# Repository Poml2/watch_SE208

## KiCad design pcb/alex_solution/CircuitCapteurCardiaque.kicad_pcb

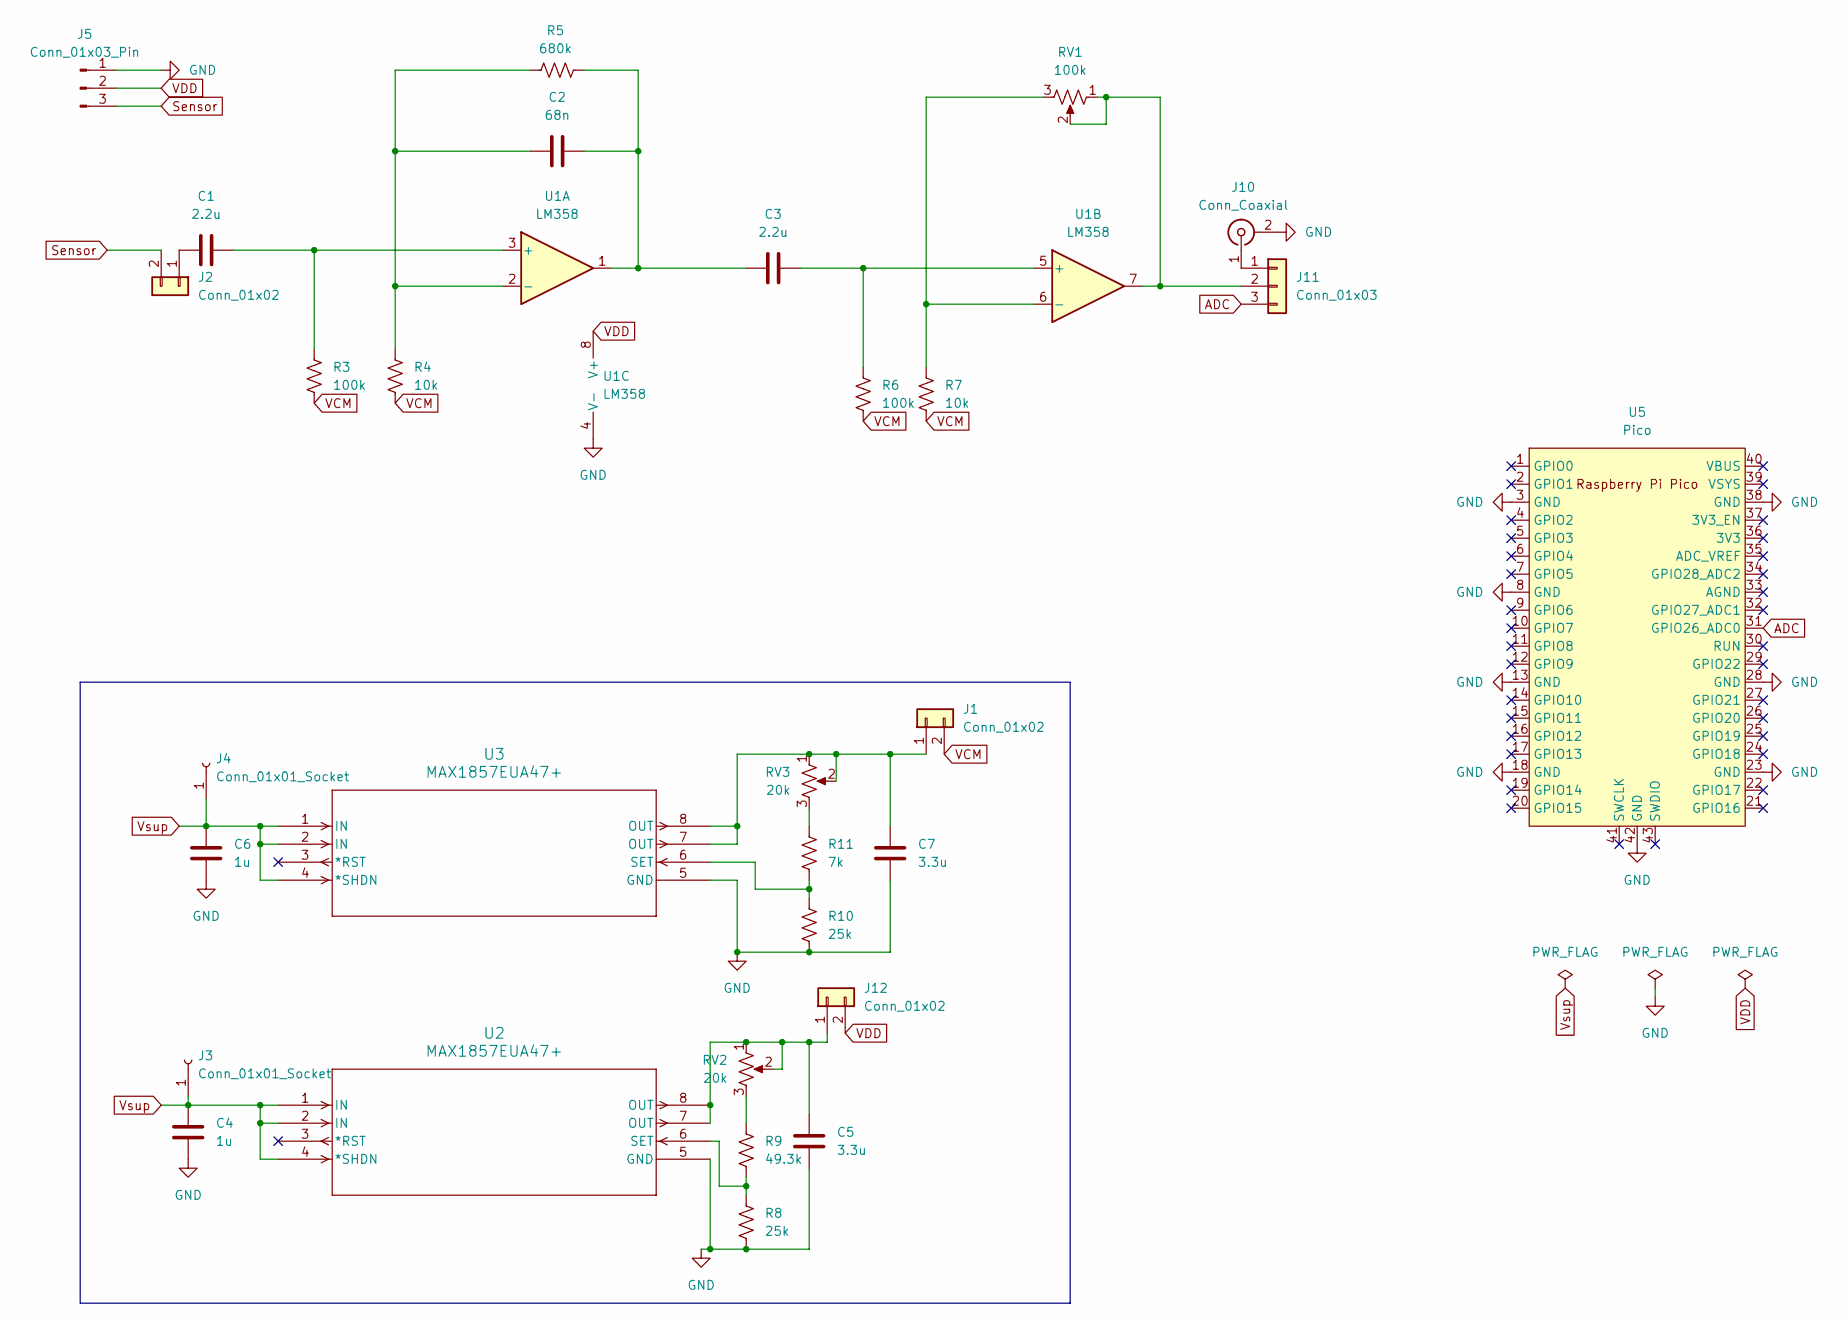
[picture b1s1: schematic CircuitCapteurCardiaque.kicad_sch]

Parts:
C1, C3: 2.2u; C_1206_3216Metric
C2: 68n; C_1206_3216Metric
C4, C6: 1u; C_1206_3216Metric
C5, C7: 3.3u; C_1206_3216Metric
J1, J2, J12: Conn_01x02; PinHeader_1x02_P2.54mm_Vertical
J3, J4: Conn_01x01_Socket; MountingHole_3.5mm_Pad_TopBottom
J5: Conn_01x03_Pin; PinHeader_1x03_P2.54mm_Vertical
J10: Conn_Coaxial; BNC_PanelMountable_Vertical
J11: Conn_01x03; PinHeader_1x03_P2.54mm_Vertical
R3, R6: 100k; R_1206_3216Metric
R4, R7: 10k; R_1206_3216Metric
R5: 680k; R_1206_3216Metric
R8, R10: 25k; R_1206_3216Metric
R9: 49.3k; R_1206_3216Metric
R11: 7k; R_1206_3216Metric
RV1: 100k; Potentiometer_Bourns_3266Y_Vertical
RV2, RV3: 20k; Potentiometer_Bourns_3266Y_Vertical
U1: LM358; DIP-8_W7.62mm_Socket
U2, U3: MAX1857EUA47+; 21-0036K
U5: Pico; RPi_Pico_SMD_TH

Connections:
ADC: J11.3, U5.31 (GPIO26_ADC0)
GND: C4.2, C5.2, C6.2, C7.2, J5.1, J10.2 (Ext), R8.2, R10.2, U1.4 (V-), U2.5 (GND), U3.5 (GND), U5.3 (GND), U5.8 (GND), U5.13 (GND), U5.18 (GND), U5.23 (GND), U5.28 (GND), U5.38 (GND), U5.42 (GND)
unnamed: C2.1, C3.2, R5.1, U1.1
unnamed: C7.1, J1.1, RV3.1, RV3.2, U3.7 (OUT), U3.8 (OUT)
unnamed: C1.2, J2.1
unnamed: J10.1 (In), J11.1
unnamed: J11.2, RV1.1, RV1.2, U1.7
unnamed: C5.1, J12.1, RV2.1, RV2.2, U2.7 (OUT), U2.8 (OUT)
unnamed: R9.1, RV2.3
unnamed: R11.1, RV3.3
unnamed: C1.1, R3.1, U1.3 (+)
unnamed: C2.2, R4.1, R5.2, U1.2 (-)
unnamed: C3.1, R6.1, U1.5 (+)
unnamed: R7.1, RV1.3, U1.6 (-)
unnamed: R8.1, R9.2, U2.6 (SET)
unnamed: R10.1, R11.2, U3.6 (SET)
Sensor: J2.2, J5.3
VCM: J1.2, R3.2, R4.2, R6.2, R7.2
VDD: J5.2, J12.2, U1.8 (V+)
Vsup: C4.1, C6.1, J3.1, J4.1, U2.1 (IN), U2.2 (IN), U2.4 (*SHDN), U3.1 (IN), U3.2 (IN), U3.4 (*SHDN)

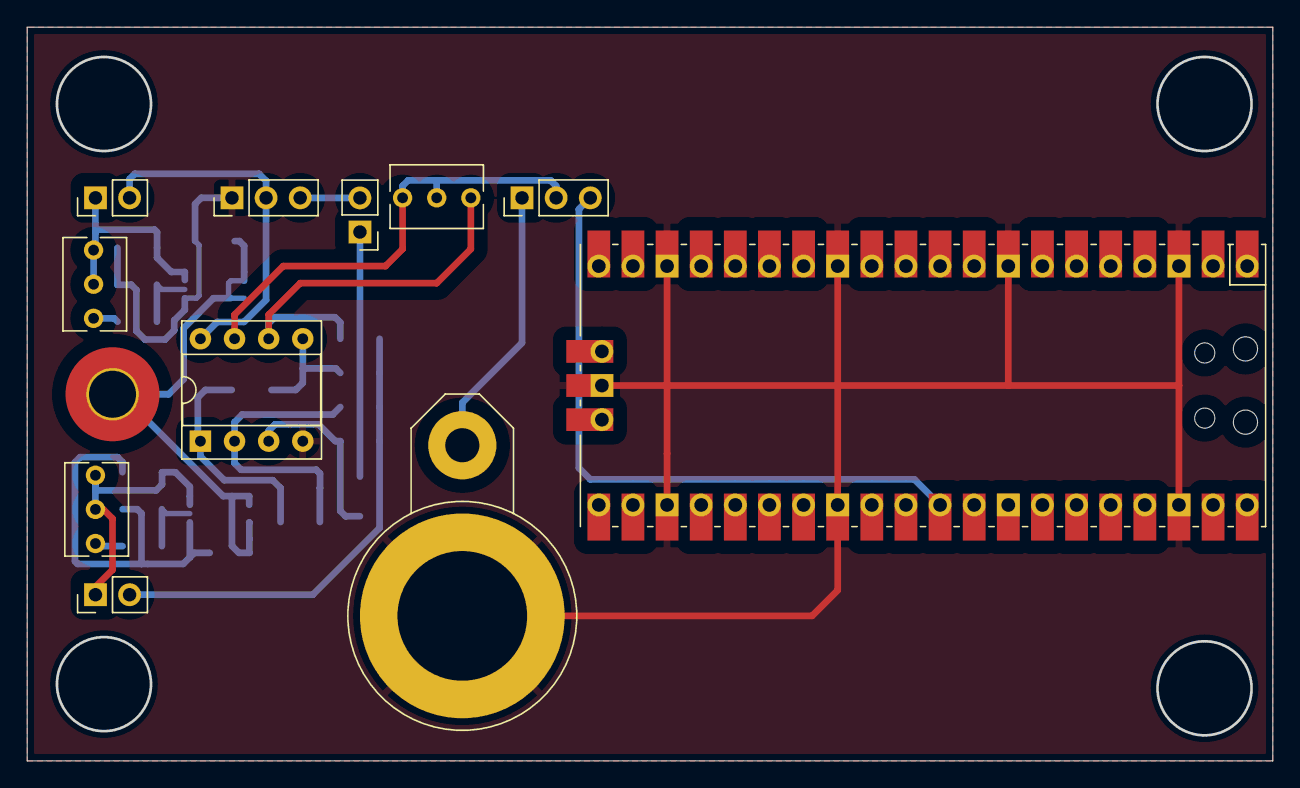
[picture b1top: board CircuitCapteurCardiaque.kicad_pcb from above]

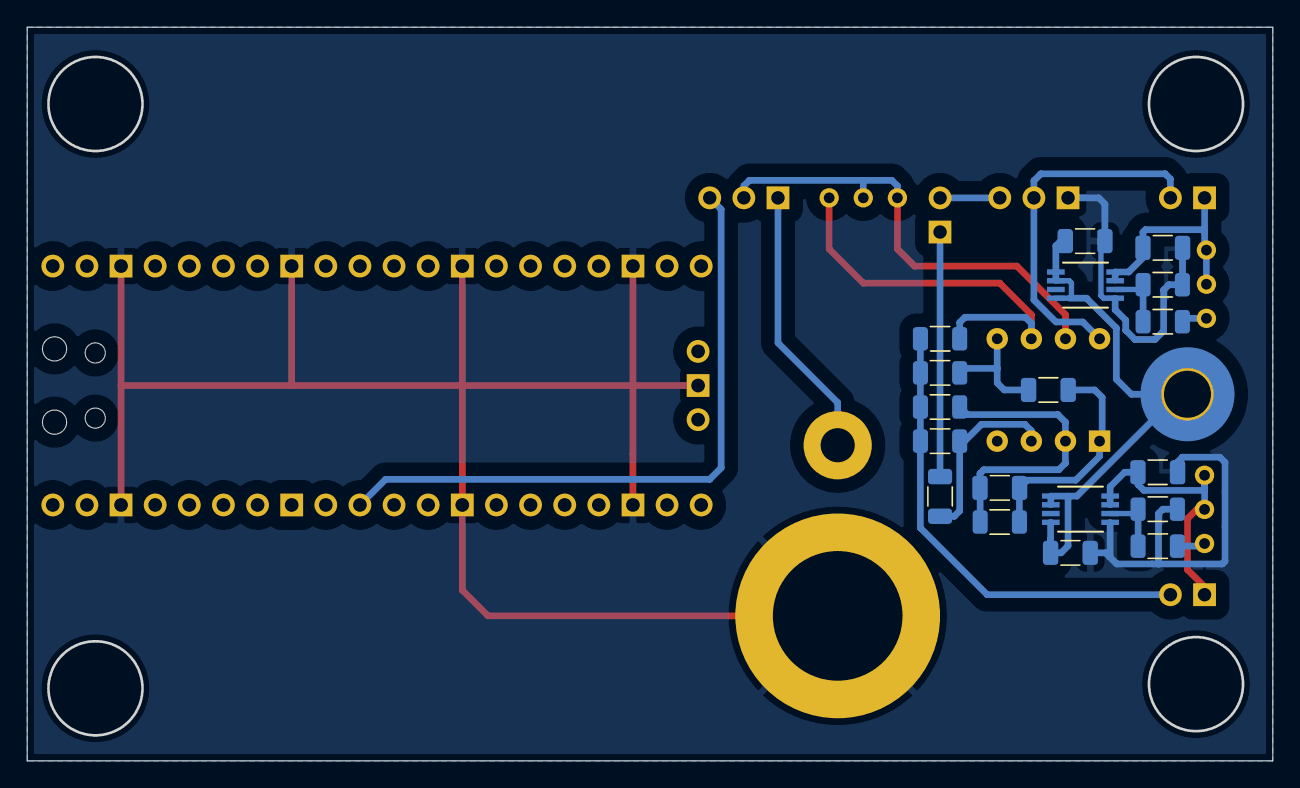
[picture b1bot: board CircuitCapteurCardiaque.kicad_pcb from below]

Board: 2 copper layers, 92.6 x 54.5 mm, 30 parts (19 on the bottom side), 20 nets.

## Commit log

2024-06-08 Add PCB
2024-06-21 Add last kicad + code folder
2024-06-21 Add code file
2024-06-21 Add graph
2024-06-22 Add files via upload
    Fonction retournant le rythme cardiaque en utilisant la FFT
2024-06-22 Update HeartRateFFT.py
    Suppression d'une ligne vide pour plus d'esthétique
2024-06-22 Corrected HeartRateFFT.py
    correction de quelques erreurs
2024-06-22 Update HeartRateFFT.py
    Suppression d'une ligne inutile
2024-06-22 Update HeartRateFFT.py
    Correction
2024-06-22 Frequence Cardiaque par detection de fronts montants
2024-06-24 Fucking bpm
2024-06-24 Filter :
2024-06-25 Update HeartRatePosedge.py
    Correction après les discussions de mardi 25/06
2024-06-25 Update HeartRateFFT.py
    Correction après les discussions de mardi 25/06
